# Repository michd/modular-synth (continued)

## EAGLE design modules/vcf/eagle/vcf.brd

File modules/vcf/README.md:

# VCF (Voltage controlled filter)

This is [Thomas Henry's VCF-1](http://www.birthofasynth.com/Thomas_Henry/Pages/VCF-1.html), with minor value changes to accomodate my power supply voltage, plus adding some inputs.

TODO: more info

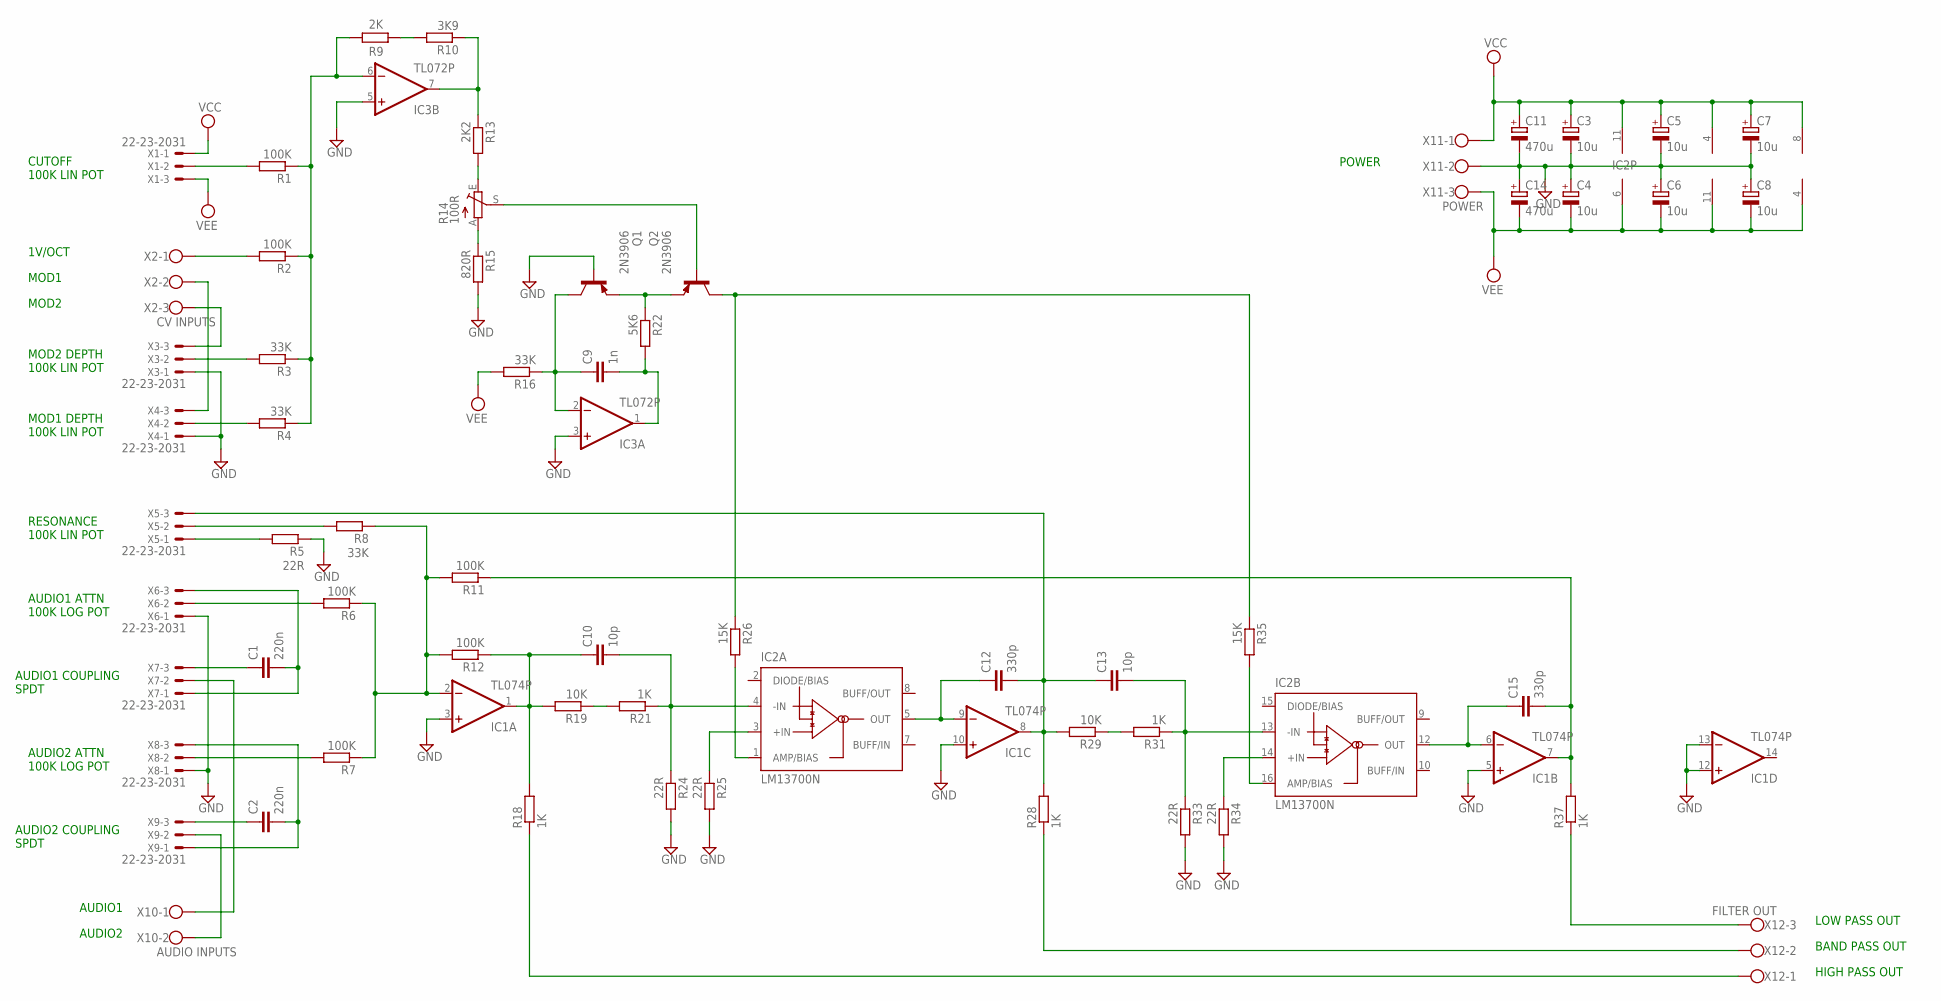
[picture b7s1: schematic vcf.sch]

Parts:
C1, C2: 220n; C025-025X050
C3, C4, C5, C6, C7, C8: 10u; E1,8-4
C9: 1n; C025-024X044
C10, C13: 10p; C025-024X044
C11, C14: 470u; E2,5-6
C12, C15: 330p; C025-024X044
IC1: TL074P; DIL14
IC2: LM13700N; DIL16
IC3: TL072P; DIL08
Q1, Q2: 2N3906; TO92
R1, R2, R6, R7, R11, R12: 100K; 0204/7
R3, R4, R8, R16: 33K; 0204/7
R5, R24, R25, R33, R34: 22R; 0204/7
R9: 2K; 0309/12
R10: 3K9; 0204/7
R13: 2K2; 0204/7
R14: 100R; CA6V
R15: 820R; 0204/7
R18, R21, R28, R31, R37: 1K; 0204/7
R19, R29: 10K; 0204/7
R22: 5K6; 0204/7
R26, R35: 15K; 0204/7
X1, X3, X4, X5, X6, X7, X8, X9: 22-23-2031
X2: CV INPUTS; W237-103
X10: AUDIO INPUTS; W237-102
X11: POWER; W237-103
X12: FILTER OUT; W237-103

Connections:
GND: C3.-, C4.+, C5.-, C6.+, C7.-, C8.+, C11.-, C14.+, IC1.3 (+IN), IC1.5 (+IN), IC1.10 (+IN), IC1.12 (+IN), IC1.13 (-IN), IC3.3 (+IN), IC3.5 (+IN), Q1.2 (B), R5.1, R15.2, R24.2, R25.2, R33.2, R34.2, X3.1, X4.1, X6.1, X8.1, X11.2
unnamed: X7.2, X10.1
unnamed: R2.2, X2.1
unnamed: X2.3, X3.3
unnamed: X2.2, X4.3
unnamed: R3.2, X3.2
unnamed: R4.2, X4.2
unnamed: R1.2, X1.2
unnamed: R9.2, R10.2
unnamed: IC3.7 (OUT), R10.1, R13.1
unnamed: R13.2, R14.E
unnamed: R14.A, R15.1
unnamed: Q1.3 (E), Q2.3 (E), R22.1
unnamed: Q2.2 (B), R14.S
unnamed: C9.2, IC3.1 (OUT), R22.2
unnamed: C9.1, IC3.2 (-IN), Q1.1 (C), R16.1
unnamed: X9.2, X10.2
unnamed: C1.1, X7.3
unnamed: C2.1, X9.3
unnamed: C1.2, X6.3, X7.1
unnamed: C2.2, X8.3, X9.1
unnamed: R6.2, X6.2
unnamed: R7.2, X8.2
unnamed: C10.1, IC1.1 (OUT), R12.1, R18.2, R19.2
unnamed: R19.1, R21.2
unnamed: C10.2, IC2.4 (-IN), R21.1, R24.1
unnamed: IC2.3 (+IN), R25.1
unnamed: IC2.1 (AMP/BIAS), R26.2
unnamed: IC1.2 (-IN), R6.1, R7.1, R8.1, R11.2, R12.2
unnamed: C12.1, IC1.9 (-IN), IC2.5 (OUT)
unnamed: R29.1, R31.2
unnamed: C13.2, IC2.13 (-IN), R31.1, R33.1
unnamed: R5.2, X5.1
unnamed: IC2.14 (+IN), R34.1
unnamed: IC2.16 (AMP/BIAS), R35.2
unnamed: Q2.1 (C), R26.1, R35.1
unnamed: C15.1, IC1.6 (-IN), IC2.12 (OUT)
unnamed: R8.2, X5.2
unnamed: C12.2, C13.1, IC1.8 (OUT), R28.2, R29.2, X5.3
unnamed: C15.2, IC1.7 (OUT), R11.1, R37.2
N$BP-OUT: R28.1, X12.2
N$EXP-CV: IC3.6 (-IN), R1.1, R2.1, R3.1, R4.1, R9.1
N$HP-OUT: R18.1, X12.1
N$LP-OUT: R37.1, X12.3
VCC: C3.+, C5.+, C7.+, C11.+, IC1.4 (V+), IC2.11 (V+), IC3.8 (V+), X1.1, X11.1
VEE: C4.-, C6.-, C8.-, C14.-, IC1.11 (V-), IC2.6 (V-), IC3.4 (V-), R16.2, X1.3, X11.3

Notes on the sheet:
POWER
CUTOFF 100K LIN POT
1V/OCT
MOD1
MOD2
MOD1 DEPTH 100K LIN POT
MOD2 DEPTH 100K LIN POT
AUDIO1 ATTN 100K LOG POT
AUDIO2 ATTN 100K LOG POT
AUDIO1 COUPLING SPDT
AUDIO2 COUPLING SPDT
AUDIO1
AUDIO2
RESONANCE 100K LIN POT
LOW PASS OUT
BAND PASS OUT
HIGH PASS OUT

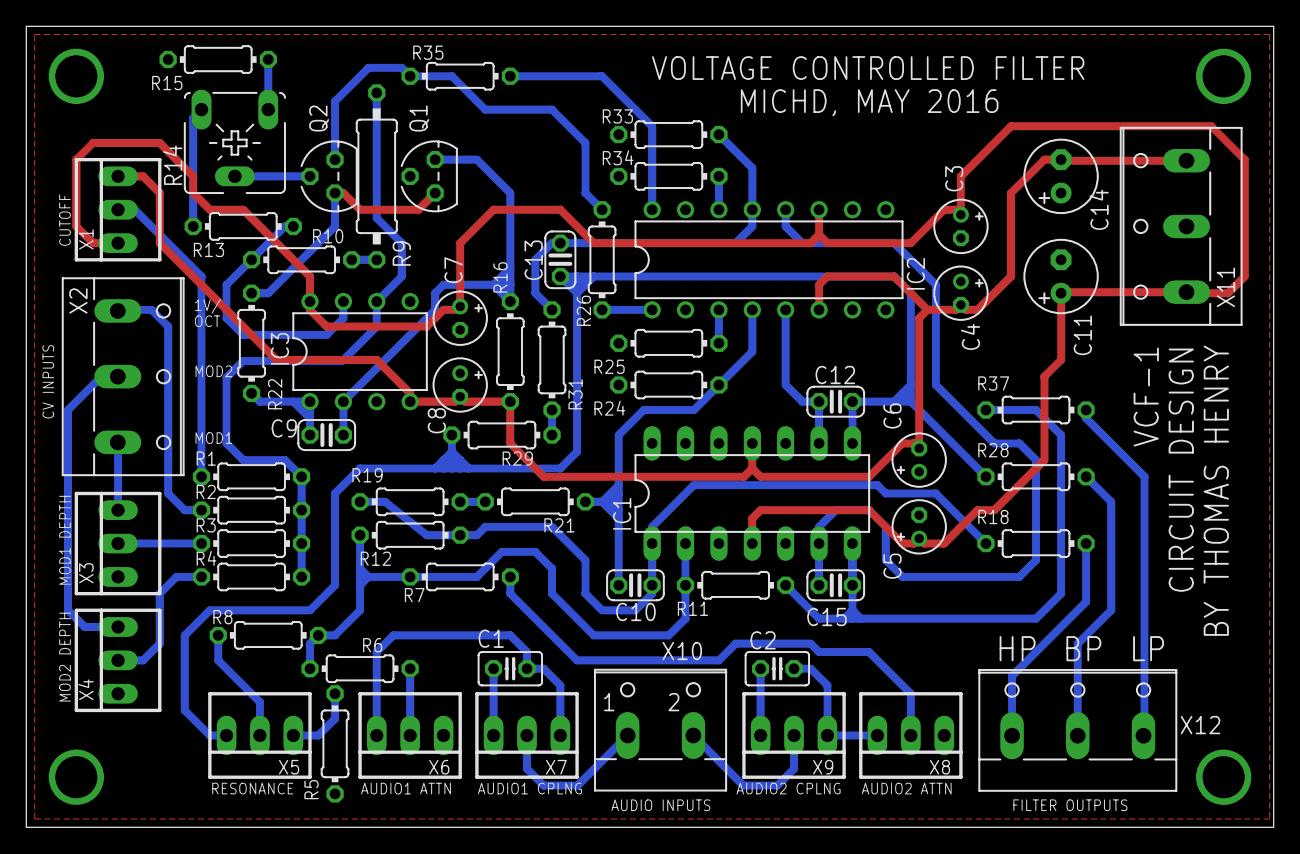
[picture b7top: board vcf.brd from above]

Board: 2 copper layers, 94.9 x 61.0 mm, 62 parts (0 on the bottom side), 46 nets.

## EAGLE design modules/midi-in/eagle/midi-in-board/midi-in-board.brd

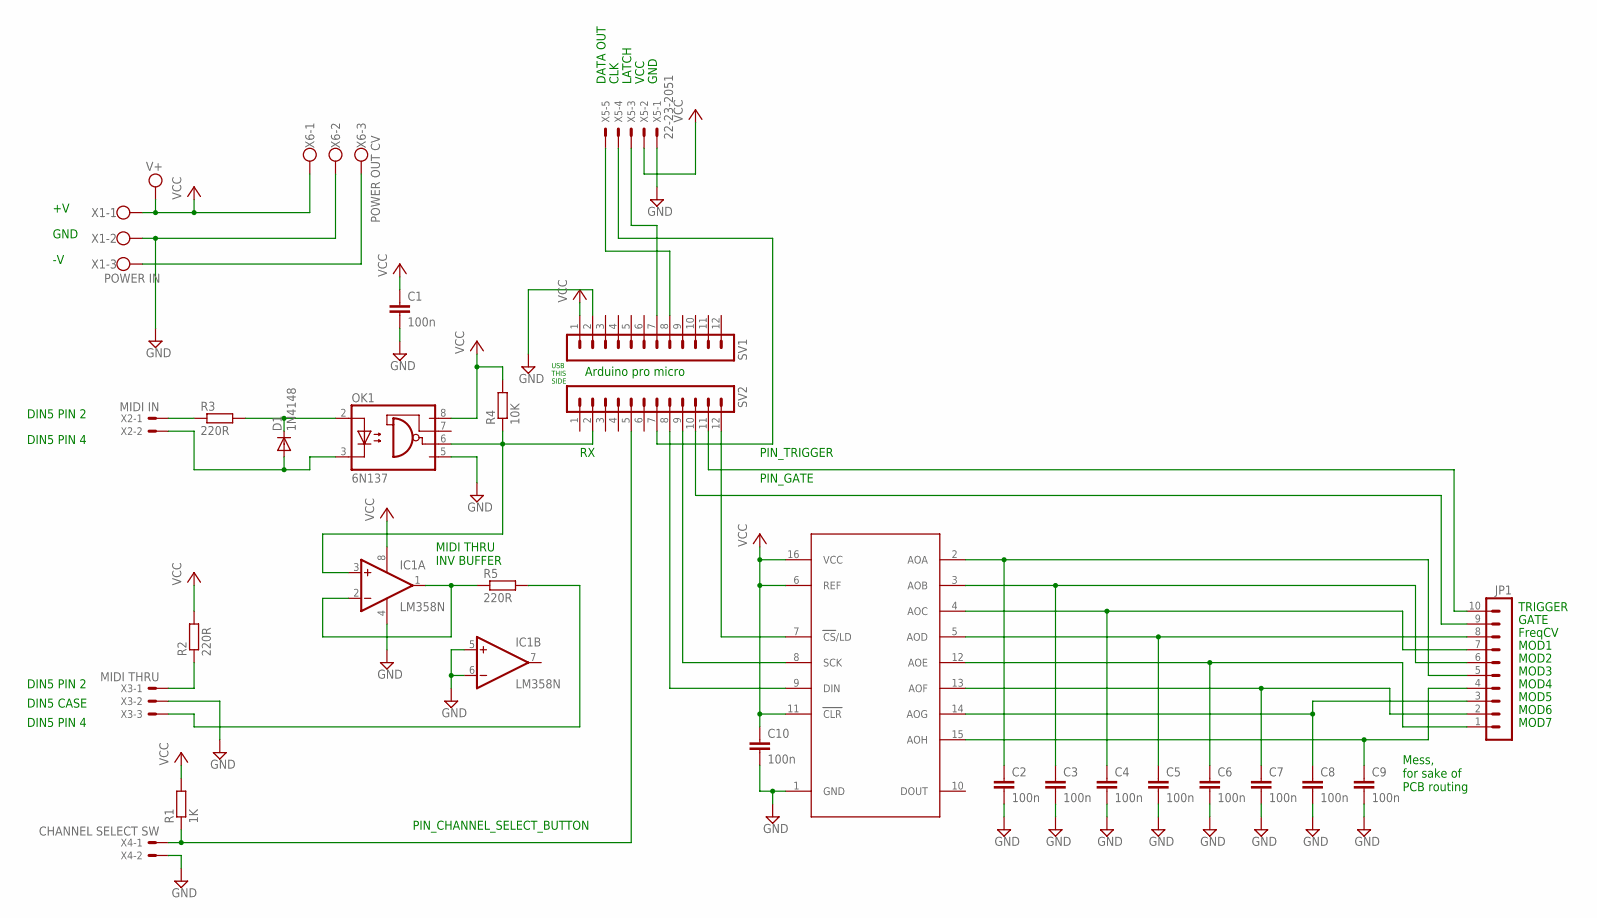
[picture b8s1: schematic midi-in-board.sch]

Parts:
C1, C2, C3, C4, C5, C6, C7, C8, C9, C10: 100n; C050-024X044
D1: 1N4148; DO35-7
IC1: LM358N; DIL08
JP1: MA10-1
OK1: 6N137; DIL08
R1: 1K; 0207/7
R2, R3, R5: 220R; 0207/7
R4: 10K; 0207/7
SV1, SV2: MA12-1
U$1: LTC1660; DIL16
X1: POWER IN; W237-103
X2: MIDI IN; 22-23-2021
X3: MIDI THRU; 22-23-2031
X4: CHANNEL SELECT SW; 22-23-2021
X5: 22-23-2051
X6: POWER OUT CV; W237-103

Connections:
GND: C1.2, C2.2, C3.2, C4.2, C5.2, C6.2, C7.2, C8.2, C9.2, C10.2, IC1.4 (V-), IC1.5 (+IN), IC1.6 (-IN), OK1.5 (GND), SV1.2, U$1.1 (GND), X1.2, X3.2, X4.2, X5.1, X6.2
unnamed: R3.1, X2.1
unnamed: D1.C, OK1.2 (A), R3.2
unnamed: D1.A, OK1.3 (C), X2.2
unnamed: IC1.1 (OUT), IC1.2 (-IN), R5.1
unnamed: IC1.3 (+IN), OK1.6 (VO), R4.1, SV2.2
unnamed: R2.1, X3.1
unnamed: R5.2, X3.3
unnamed: SV1.8, X5.5
unnamed: X1.3, X6.3
unnamed: JP1.10, SV2.11
unnamed: JP1.9, SV2.10
unnamed: R1.1, SV2.5, X4.1
unnamed: SV2.9, U$1.8 (SCK)
unnamed: SV2.8, U$1.9 (DIN)
unnamed: C2.1, JP1.5, U$1.2 (AOA)
unnamed: SV2.12, U$1.7 (CS/LD)
unnamed: SV2.7, X5.4
unnamed: SV1.7, X5.3
unnamed: C3.1, JP1.6, U$1.3 (AOB)
unnamed: C6.1, JP1.1, U$1.12 (AOE)
unnamed: C4.1, JP1.7, U$1.4 (AOC)
unnamed: C5.1, JP1.8, U$1.5 (AOD)
unnamed: C7.1, JP1.2, U$1.13 (AOF)
unnamed: C8.1, JP1.3, U$1.14 (AOG)
unnamed: C9.1, JP1.4, U$1.15 (AOH)
VCC: C1.1, C10.1, IC1.8 (V+), OK1.8 (VCC), R1.2, R2.2, R4.2, SV1.1, U$1.6 (REF), U$1.11 (CLR), U$1.16 (VCC), X1.1, X5.2, X6.1

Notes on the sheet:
DIN5 PIN 2
DIN5 PIN 4
DIN5 CASE
Arduino pro micro
LATCH
DATA OUT
PIN_TRIGGER
PIN_GATE
CLK
PIN_CHANNEL_SELECT_BUTTON
USB THIS SIDE
MIDI THRU INV BUFFER
GND
VCC
TRIGGER
GATE
FreqCV
MOD1
MOD2
MOD3
MOD4
MOD5
MOD6
MOD7
Mess, for sake of PCB routing

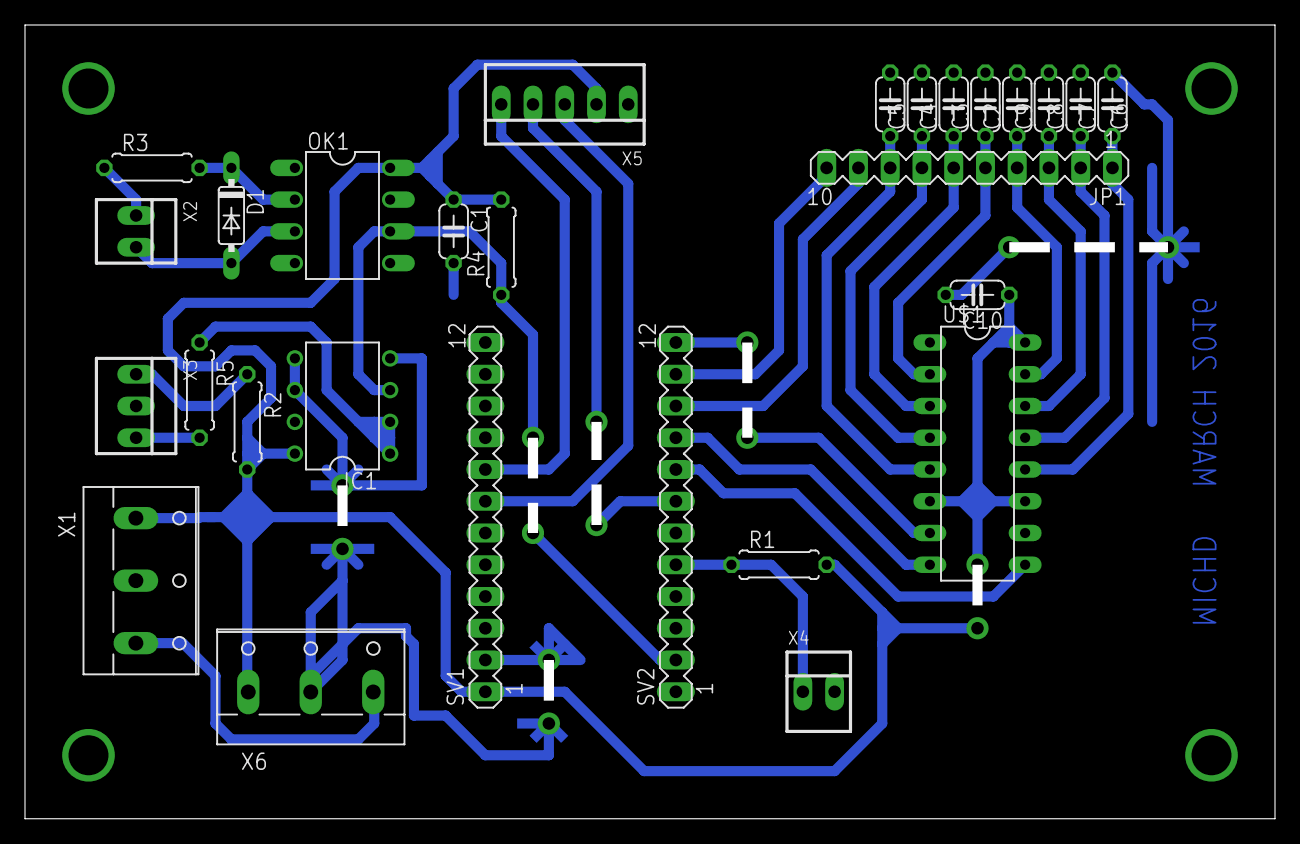
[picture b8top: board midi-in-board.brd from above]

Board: 2 copper layers, 99.2 x 62.7 mm, 28 parts (0 on the bottom side), 27 nets.

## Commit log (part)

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2015-07-18 Initial commit
    Adding quick readme and gitignore for eagle and sketchup
2015-07-19 Synth enclosure design in sketchup
2015-07-19 Add power panel to enclosure design
    Includes SVG design fit for ponoko.com or razorlab.co.uk, for laser
    cutting/engraving
2015-07-26 Add power supply design
    This includes an LTSpice simulation in simulations/
    and a schematic and PCB in eagle/
2015-07-26 Add some documentation to the power supply folder (partlist etc)
2015-08-16 Update power supply board designs to allow heatsinks
2015-09-23 Fixes to power supply circuit and board design
2015-09-23 Design schematic for patch panel
2015-12-05 Fix patch panel design to use correct pot pin
2016-02-23 Add some experimental 7seg code for midi in
2016-02-23 Add midi in tests, rejuggle arduino files
2016-02-23 Add button channel increment test to midi in 7seg test
2016-02-23 Fix up 7seg test to be less hacky, more reliable
2016-02-23 Move 7 segment / channel control code into midi-in
    Some TODO left, actually applying the selected channel to the messages
    listened for, and of course, outputting relevant PWM.
2016-02-24 MIDI in: Ignore messages for not selected channel
    Further, the midi channel is now stored as 0-15 instead of 1-16.
    MIDI messages have it as 0-15, and 1-16 is only used for user-facing.
    We're still displaying it as 1-16 on the display, of course.
2016-02-26 MIDI in: use MIDI library, listen for control changes
    After a bit too much misery relating to reinventing things, I've caved
    in and added a prebuilt MIDI library, which works like a charm.
    MIDI channels are once again 1-indexed, as that's how this MIDI library
    does it.
    Also new is listening to control changes, and outputting them.
2016-02-27 MIDI-in: optimizations, midi-refactoring, pitch-bend
2016-02-28 MIDI in: Output frequency control voltage, active note stack
    Pre-calculates all the values needed to map available notes to output
    values that will map to 1V/Oct voltages.
    The note stack allows up to 24 (well, actually 25) notes to be held at a
    time, letting you release the latest note to return to the previously
    pressed note, as long as it's still held down.
    Further, this documents the code a bit more.
2016-02-28 Fix missing param type in outputPitchBend
2016-02-28 [WiP] midi in main board schematic
2016-02-29 Update power-panel-face using razorlab template
2016-03-01 Finish up midi in board schematic, for now
2016-03-01 Added shift registers, start-up reset on display board schematic
    TODO: revise the board, revise the main schematic
2016-03-01 Redesign display board layout w/ shift registers
2016-03-02 Start PCB design for main MIDI in board
2016-03-03 Progress on MIDI in main board. Nightmare.
2016-03-03 Separate out CV scaling to its own board, finish MIDI in board layout
    Non-nightmare!
2016-03-03 Add MIDI-in board section to MIDI in readme
2016-03-05 Probably doomed attempt at routing CV board.
2016-03-15 Finish CV board,
2016-03-15 Add MIDI in front and back panel designs
    Specifically, SVG in Inkscape, the way Razorlab.co.uk (or Ponoko) like
    them.
2016-03-16 MIDI-in code: use external DAC rather than PWM outputs
    PCB updates to follow.
2016-03-17 Redesign of MIDI in board, now with DAC.
    Remapped the names of DAC channels, for more straightforward PCB routing.
2016-04-02 Add VCO ltspice simulation
2016-04-06 Move things around, PSU -> modules, remove patch-panel
2016-04-06 [WiP] started VCO schematic design in eagle
2016-04-06 Finish up 1x VCO schematic in eagle
2016-04-10 Design front panel for VCO
2016-04-18 Output velocity on MOD3 (midi in module)
2016-04-23 VCO PCB fixes
    - Fixes a couple of design flaws: two opamps hade the inputs the wrong way
    around, the sine output net intersected with a pin connected to ground
    - Moves the connector legend to the tName layer so they show up in fab.
    - Adds legends to the trimpots
2016-04-23 Update pot drill holes in VCO paneling, for new pots
    Also add another SVG with visibly thick lines for cuts plus drill sizes,
    for use on manually cutting an aluminium panel
2016-04-23 Remove VCO panel PNG exports
2016-04-30 Badly finish VCF board layout (single)
2016-05-21 Redesign filter board without limitiers; double-sided
    The single-sided board with limiters didn't work. The limiters
    introduced DC offsets that made various opamps just max out, creating a
    static DC output. The limiting circuitry is now removed, and the new PCB
    design is a double-sided one because I could not be bothered making
    another terrible single-sided one.
2016-05-21 Add panel design for filter, based on the oscillator one
2016-05-25 Fix pwm amount input on VCO
2016-10-03 Add control voltage helper module
2016-10-03 Add mixer module, well, paneling
2016-10-04 Add schematic for dual vca module
2016-10-06 Basic layout of VCA board, still needs power
2016-10-06 VCA board: drop symmetry in favor of smaller size
2016-10-24 Add SVG helper for eurorack dimensions
2016-10-25 Finish most of midi in panel eurorack conversion
2016-10-27 Finalize MIDI IN eurorack version + display breakout board
2016-10-27 Design front panel for VCA
2016-10-28 Add markings around pot to panel design helpers
2016-10-29 Fix display board screw spacing on midi in front panel
2016-10-29 Update laser front panel designs for SMI's laser cutter
2016-10-30 Add another knob size to the panel design helpers
2016-10-30 Add new eurorack front panel design for VCO
2016-11-04 Add power distribution board
2016-11-04 Add eurorack vcf panel
2016-11-12 Add audio output module (just panel)
2016-11-12 Fix screw hole position in VCO panel
2016-11-12 Add power helper utility module (just panel)
2016-11-23 Update CV helper paneling for eurorackify
2016-11-23 Remove old enclosure model
2016-11-23 Cleanup and renaming in modules
2016-11-29 Add kicad schematic for ADSR module
    Based on MFOS ADSR generator, but with a feature by yours truly: in-pot
    LEDs indicating the current state in the ADSR cycle. Designed for use
    with Bourns PTL-series slide pots.
2016-11-29 Add some info for the slide pots to be used
2016-11-29 Initial panel design for dual ADSR module
    Will likely change as I go through the PCB design to go with it.
2017-01-08 Add gitignore stuff for kicad
2017-01-08 [WiP] ADSR board layout
2017-01-11 Add schematic and board for noise generator
2017-01-14 Add noise generator front panel
2017-01-21 Redo ADSR generator PCB layout
2017-01-21 Fix up ADSR panel for completed PCB design
2017-04-26 Add second revision of adsr module
2017-05-28 Finish up ADSR generator schematic, PCB, replace broken one
2017-05-29 Add schematic for reverb module
2017-05-31 Reverb PCB: footprint assignments
2017-06-01 Lay out reverb PCB
2017-06-02 Correct some component values on reverb schematic/pcb
2017-06-11 Small tweaks to reverb pcb config
2017-06-11 Reverb: Fix LM13700 power connections inverted
    The power pins on the LM13700 OTA were the wrong way around. This causes
    the LM13700 to, well, break. it'll heat up a bit and of course not
    function.
2017-06-11 Add inverter utility module (schematic, pcb, panel)
2017-06-13 Add some falstad circuit simulations for foldback distortion
2017-08-05 Design full circuit diagram in falstad simulator
2017-08-05 Draw distortion circuit in kicad, pcb wip
2017-08-05 Distortion pcb: panelization stuff, started layout wip
2017-08-05 Distortion: move some resistors to top board WIP
2017-08-05 Distortion: finishing routing pcb and silkscreen
2017-08-06 Round edges for panelizing mousebits in distortion pcb
2017-08-23 [wip] Sequencer code: add quantization
2017-08-26 Sequencer code: cleanup + software debouncing and input cleanup
2017-08-26 Sequencer code: Timer-based tempo, gate mode selection
2017-08-27 Sequencer: add step repeat function
2017-09-09 Sequencer: Add input caching to port expander lib
    No longer doing SPI work in loop() now
2017-09-10 MCP23S17 lib: implement interrupt functionality
    Also now using some neater arduino data type aliases like word and byte
2017-09-10 Sequencer: code: move couple of buttons to portexp
2017-10-15 Fix SPI interference with some terrible boolean flags
2017-10-16 Add integration for 7 segment display
2017-10-22 Add PTV09 to panel design helpers
2017-10-22 Final tweaks to distortion pcb
2017-10-22 Tweaks to distortion front panel
2017-10-22 More detail about PTV09 pot for distortion
2017-10-22 Remove some accidentally committed fab files
2017-10-28 Big refactor, sequencer and io into their own modules
2017-11-01 MAX72S19: add support in print for "."
2017-11-01 Move note mapping to its own module; show current note
2017-11-13 Start clock generator module code for ATTiny84
2017-11-13 Add ISP connector to hardware.txt for clock gen
2017-11-17 New plain AVR-C project for clock generator
2017-11-17 Use external clock in sequencer
2017-11-17 Map PPQ out in clock generator to correct pin
2017-11-17 Remove TimerOne dependency
2017-11-18 Clock gen pcb: routed all but the power nets
2017-11-19 Finish clock generator PCB, start panel
2017-12-12 Output 32th notes from uC in clock generator
2018-01-06 Clock gen: finish pcb, panel, arrow buttons
2018-01-15 Sequencer: add scale select button
    Allows cycling through hardcoded scales the NoteMapper is constrained to.
    Adds some extra scales to it too.
2018-01-17 Fix flank detection for port expander
    It was inverted.
2018-01-17 Add settings struct/manager to load/save from/to eeprom
2018-01-17 Implement reset/load/save actions
    Load / save:
    There are 9 (NUM_STEPS + 1 memory locations to store the sequencer's
    full settings, each accessible through the sequencer's step buttons.
    To load a "patch": hold a step button, then press load. This loads the
    corresponding patch.
    If no step button is held, location 0 is used.
2018-01-17 Sequencer code cleanup + reset behavior tweaks
    I spent like 10 minutes trying to manually edit the patch to separate out
    the char array -> string changes into its own commit but failed
    horiffically, so it's just in this commit.
    Anyway:
    - For all the writeDisplay needs, String is now used, instead of
    cumbersome plain char arrays. It adds some program space overhead, but
2018-01-20 Lower sequencer screen brightness
    Replaced with a smaller, red screen that happens to be much brighter
2018-01-20 Replace longwinded procedural sequences with hardcoded
    Sequence modes are now done with much easier to follow hardcoded arrays
    instead of a long-winded procedural method relying on remembering the
    previous step.
2018-01-20 Add constants for DEF. MIN/MAX note in NoteMapper
    Note: I already used them in an earlier commit, but forgot to commit
    them in the header file then.
2018-01-20 Fix sequence not updating when loading patch
2018-01-22 MAX72S19->MAX7221
2018-01-25 Sequencer: implement chaining functionality
2018-01-25 Sequencer display driver: init display cache to all on
    This ensures that clearing the display initially actually works, because
    on startup there's sometimes garbage in those registers in the chip. If
    the cache is 0x00 it thinks they're already cleared and doesn't actually
    write to them.
2018-01-25 Debounce buttons in IO module
2018-01-25 Fix display bug when holding step and changing its settings
    it would instantly go back to displaying the note. No longer.
    Plus some cleanup for less repetitive writing notes to display.
2018-01-26 Sequencer: add output determining chained routing
    Switches the pitch/velocity/gate/trigger outputs between local and
    chained inputs
2018-01-30 [wip] sequencer pcb and panel
2018-01-30 Finish initial panel layout of sequencer
2018-02-03 Add slide function to sequencer panel
2018-02-03 [WiP] Sequencer schematic
2018-02-04 Finish Sequencer schematic
2018-02-16 Most of sequencer PCB design + aligning stuff with panel
    Still need to route power connections
2018-02-18 Add screw holes to seq. PCB, finish panel alignment
2018-02-18 Finish routing nets on sequencer PCB
    TODO: silkscreen
